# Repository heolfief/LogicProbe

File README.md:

# Logic probe
**Three state logic probe**

This is a NAND based three state logic probe with an optional buzzer.

The three states are : 
* HIGH         --  Green LED
* LOW          --  Red LED
* UNDETERMINED --  Blue LED

The undetermined step is active when the probe can't figure out if the signal probed is high or low (floating), or when the signal is switching quickly between the two (PWM).

The ".sch"(schematics) and ".brd"(board layout) files are in **Autodesk Eagle 8.0** format.

The PCB can be made of a single sided copper board. Components packages are 1206, 0805, SO14 and SOT23-3.

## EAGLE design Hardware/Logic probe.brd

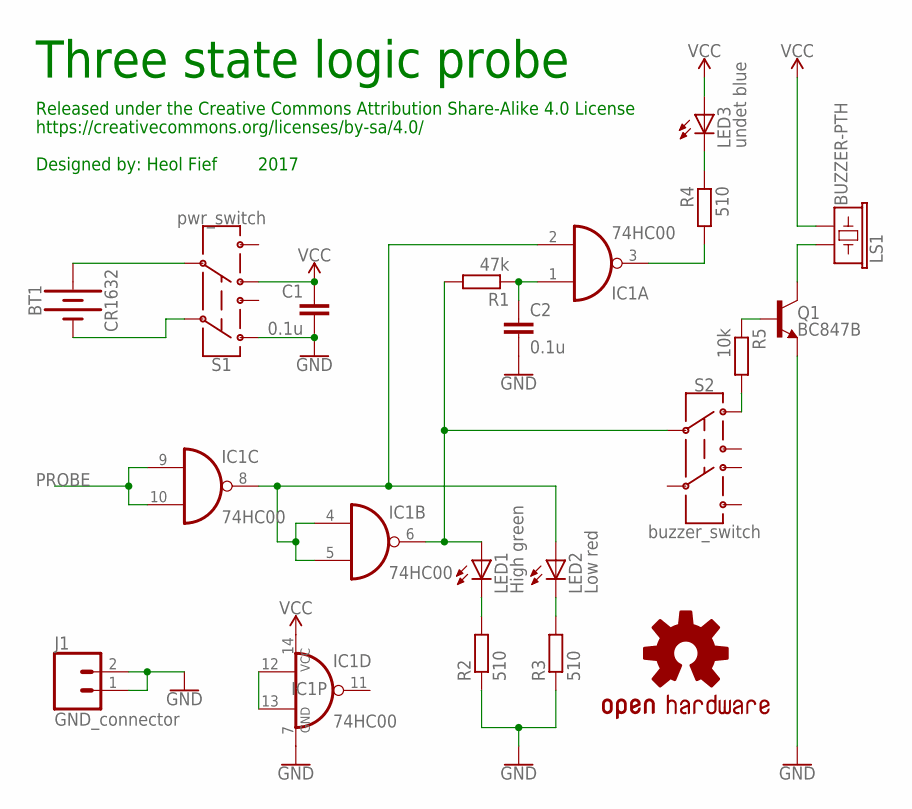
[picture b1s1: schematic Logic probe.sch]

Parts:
BT1: CR1632; BATTCON_16MM_PTH
C1, C2: 0.1u; C0805
IC1: 74HC00; SO14
J1: GND_connector; MOLEX-1X2
LED1: High green; 1206
LED2: Low red; 1206
LED3: undet blue; 1206
LOGO1: OSHW-LOGOL; OSHW-LOGO-L
LS1: BUZZER-PTH; BUZZER-12MM
Q1: BC847B; SOT23-3
R1: 47k; R1206
R2, R3, R4: 510; R0805
R5: 10k; R0805
S1: pwr_switch; SWITCH_DPDT_SMD_AYZ0202
S2: buzzer_switch; SWITCH_DPDT_SMD_AYZ0202

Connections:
GND: C1.2, C2.2, IC1.7 (GND), J1.1, J1.2, Q1.2 (E), R2.1, R3.1, S1.1
unnamed: LED3.C, R4.2
unnamed: R5.2, S2.1
unnamed: IC1.2 (I1), IC1.4 (I0), IC1.5 (I1), IC1.8 (O), LED2.A
unnamed: Q1.1 (B), R5.1
unnamed: LS1.+ (1), Q1.3 (C)
unnamed: BT1.GND (-), S1.2
unnamed: C2.1, IC1.1 (I0), R1.1
unnamed: LED1.C, R2.2
unnamed: IC1.3 (O), R4.1
unnamed: LED2.C, R3.2
unnamed: BT1.VCC@1 (+), BT1.VCC@2 (+), S1.5
unnamed: IC1.12 (I0), IC1.13 (I1)
unnamed: IC1.6 (O), LED1.A, R1.2, S2.2
PROBE: IC1.9 (I0), IC1.10 (I1)
VCC: C1.1, IC1.14 (VCC), LED3.A, LS1.- (2), S1.4

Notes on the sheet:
Released under the Creative Commons Attribution Share-Alike 4.0 License
https://creativecommons.org/licenses/by-sa/4.0/
Designed by: Heol Fief 2017
Three state logic probe

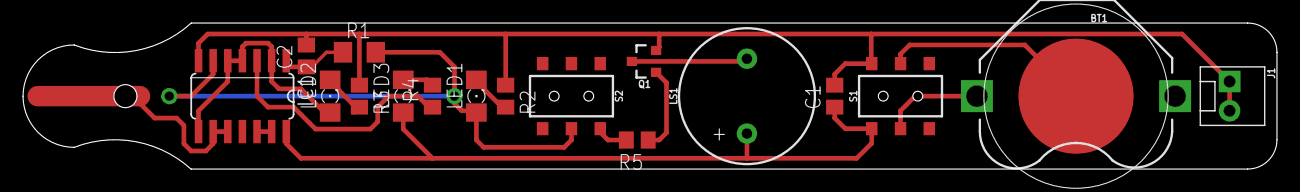
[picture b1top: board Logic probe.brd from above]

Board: 2 copper layers, 108.9 x 12.7 mm, 18 parts (0 on the bottom side), 16 nets.

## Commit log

2017-02-04 Update README.md
    Edit project description
2017-02-04 Add files via upload
    Eagle schematics and board layout files
2017-02-04 Add files via upload
    Schematics PDF
2017-02-04 Add files via upload
    Schematics in PDF format
2017-02-04 Update README.md
    Add Autodesk Eagle format mention
2017-02-04 Update README.md
    Format
2017-02-04 Create LICENSE.md
    Add license information
2017-02-04 Update LICENSE.md
    Add OSHW logo
2017-02-05 Create A
2017-02-05 Add files via upload
    Add hardware files
2017-02-05 Delete Logic probe schematics.pdf
    moved to hardware folder
2017-02-05 Delete Logic probe.brd
    moved to hardware folder
2017-02-05 Delete Logic probe.sch
    moved to hardware folder
2017-02-05 Add files via upload
    Add BOM
2017-02-05 Update README.md
    Add hardware description (PCB and packages)
2017-02-06 Update README.md
    Fix package type
2017-02-07 Update README.md
    Mention about floating and PWM
2017-02-07 Add files via upload
    Fix buzzer circuit
2017-02-17 Add files via upload
    Change battery size & probe lenght
2017-02-17 Add files via upload
    Change battery size
2017-03-04 Add files via upload
    Change formating

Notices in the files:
parts and their libraries:
SparkFun-DiscreteSemi: Licensing: Creative Commons ShareAlike 4.0 International - https://creativecommons.org/licenses/by-sa/4.0
